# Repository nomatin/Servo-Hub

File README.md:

# Servo Hub

This is an older project that I updated slightly before publishing.

Eight-channel servo power and signal hub. A TPS54821RHLR converts a nominal 12 V input to 5 V, while S1–S8 pass directly from the controller to the servos.

- Input voltage — 12 V nominal, 17 V maximum.
- Output voltage — 5 V.
- Maximum total servo current — 8 A (design limit).

## 3D View

## PCB Topology

| Top copper and silkscreen | Bottom copper and silkscreen |
| --- | --- |
|  |  |

## Pinout

| Connector | Pins |
| --- | --- |
| J1 · XT30 power input | 1 = GND, 2 = VIN |
| J2 · PicoBlade controller input | 1–8 = S1–S8, 9 = +5 V, 10 = GND |
| J5 · Servo outputs | `S` = signal, `+` = 5 V, `−` = GND |

J2 pin 9 shares the servo 5 V rail. Check for backfeeding if the controller has a separate supply.

## Project files

- [KiCad 9 project](board/servo_manager.kicad_pro) · [Schematic PDF](board/release/servo_manager-schematic.pdf)
- [Gerber ZIP](manufacturing/gerber/servo_manager-gerber.zip) · [Drill files](manufacturing/drill/) · [BOM](manufacturing/bom/servo_manager-bom.csv) · [Pick and place](manufacturing/pick-and-place/)

Before fabrication, reconcile the IC1 footprint link and the J2 mounting pads with the schematic.

## License

Project files are released under the [MIT License](LICENSE). Third-party libraries and 3D models retain their respective terms.

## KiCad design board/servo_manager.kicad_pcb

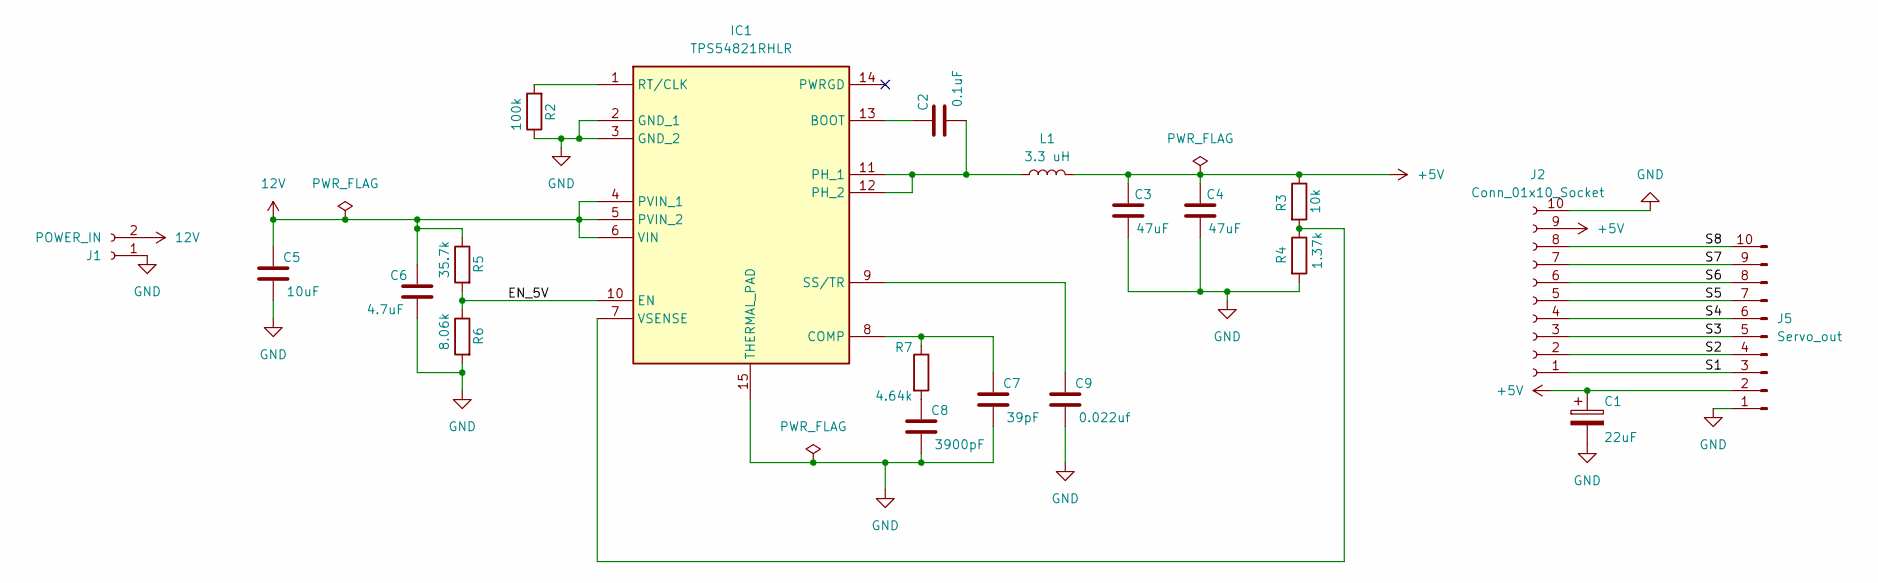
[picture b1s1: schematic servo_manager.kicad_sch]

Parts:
C1: 22uF; CP_EIA-3528-21_Kemet-B; Manufacturer_Part_Number TCJB226M025R0100
C2: 0.1uF; C_0805_2012Metric; Manufacturer_Part_Number 08055C104KAT2A
C3, C4: 47uF; C_1210_3225Metric; Manufacturer_Part_Number 12103D476MAT2A
C5: 10uF; C_0805_2012Metric; Manufacturer_Part_Number KGM21AR51E106KU
C6: 4.7uF; C_0805_2012Metric; Manufacturer_Part_Number 08055D475KAT2A
C7: 39pF; C_0805_2012Metric; Manufacturer_Part_Number 08055A390JAT4A
C8: 3900pF; C_0805_2012Metric; Manufacturer_Part_Number 08055A392FAT2A
C9: 0.022uf; C_0805_2012Metric; Manufacturer_Part_Number 08055C223MAT2A
IC1: TPS54821RHLR; TPS54622RHLR; Manufacturer_Part_Number TPS54821RHLR; Mouser Part Number 595-TPS54821RHLR
J1: POWER_IN; AMASS_XT30PW-M_1x02_P2.50mm_Horizontal; Manufacturer_Part_Number XT30PW-M
J2: Conn_01x10_Socket; Molex_PicoBlade_53261-1071_1x10-1MP_P1.25mm_Horizontal; Manufacturer_Part_Number 0532611071
J5: Servo_out; Servo_03x08; Manufacturer_Part_Number TSW-108-08-L-T-RA
L1: 3.3 uH; L_Chilisin_BMRG00131360; Manufacturer_Part_Number IHLP5050EZER3R3M01
R2: 100k; R_0805_2012Metric; Manufacturer_Part_Number RC0805FR-07100KL
R3: 10k; R_0805_2012Metric; Manufacturer_Part_Number RC0805FR-0710KL
R4: 1.37k; R_0805_2012Metric; Manufacturer_Part_Number RC0805FR-071K37L
R5: 35.7k; R_0805_2012Metric; Manufacturer_Part_Number RC0805FR-0735K7L
R6: 8.06k; R_0805_2012Metric; Manufacturer_Part_Number RC0805FR-078K06L
R7: 4.64k; R_0805_2012Metric; Manufacturer_Part_Number RC0805FR-074K64L

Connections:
12V: C5.1, C6.1, IC1.4 (PVIN_1), IC1.5 (PVIN_2), IC1.6 (VIN), J1.2, R5.1
+5V: C1.1, C3.1, C4.1, J2.9, J5.2, L1.2, R3.1
/EN_5V: IC1.10 (EN), R5.2, R6.1
/S1: J2.1, J5.3
/S2: J2.2, J5.4
/S3: J2.3, J5.5
/S4: J2.4, J5.6
/S5: J2.5, J5.7
/S6: J2.6, J5.8
/S7: J2.7, J5.9
/S8: J2.8, J5.10
GND: C1.2, C3.2, C4.2, C5.2, C6.2, C7.2, C8.2, C9.2, IC1.2 (GND_1), IC1.3 (GND_2), IC1.15 (THERMAL_PAD), J1.1, J2.10, J2.MP, J5.1, R2.1, R4.2, R6.2
unnamed: C8.1, R7.2
unnamed: C2.1, IC1.13 (BOOT)
unnamed: C7.1, IC1.8 (COMP), R7.1
unnamed: C2.2, IC1.11 (PH_1), IC1.12 (PH_2), L1.1
unnamed: IC1.1 (RT/CLK), R2.2
unnamed: C9.1, IC1.9 (SS/TR)
unnamed: IC1.7 (VSENSE), R3.2, R4.1

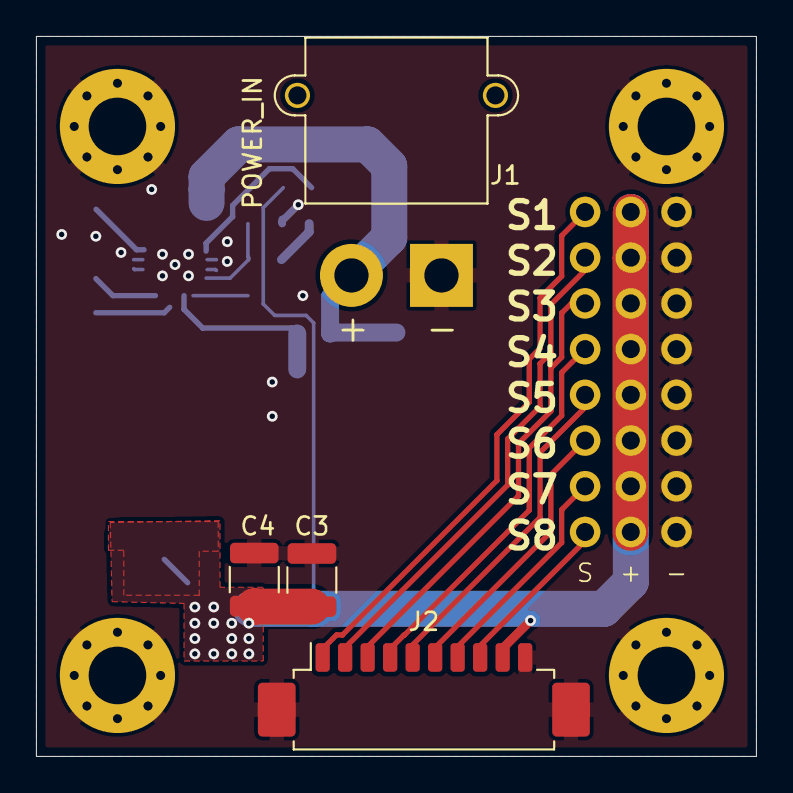
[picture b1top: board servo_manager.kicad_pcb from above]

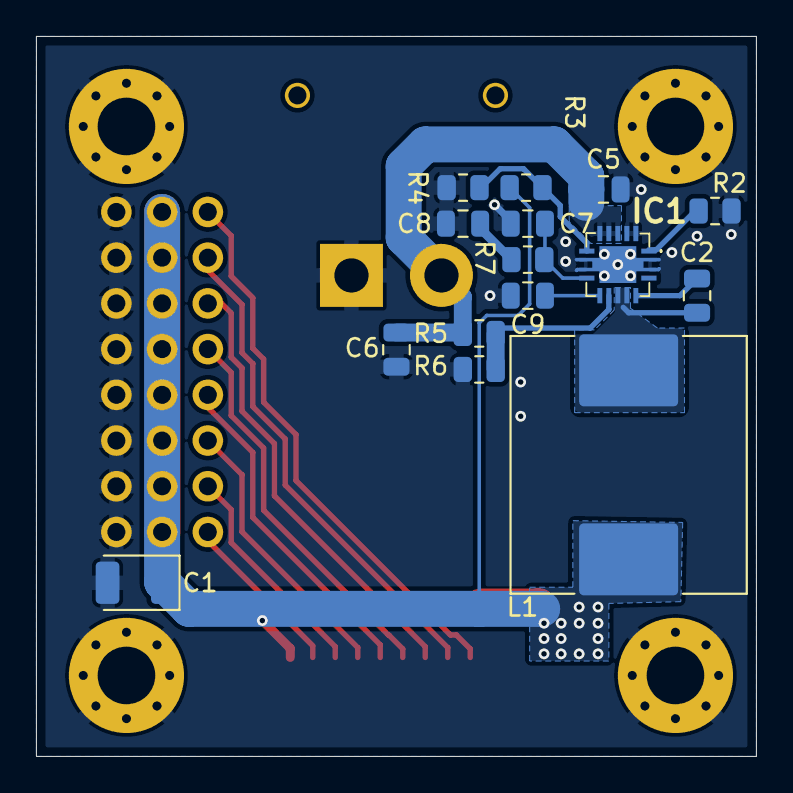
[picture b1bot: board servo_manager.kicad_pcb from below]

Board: 2 copper layers, 40.0 x 40.0 mm, 20 parts (15 on the bottom side), 19 nets.

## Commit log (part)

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2024-11-12 Первый коммит
